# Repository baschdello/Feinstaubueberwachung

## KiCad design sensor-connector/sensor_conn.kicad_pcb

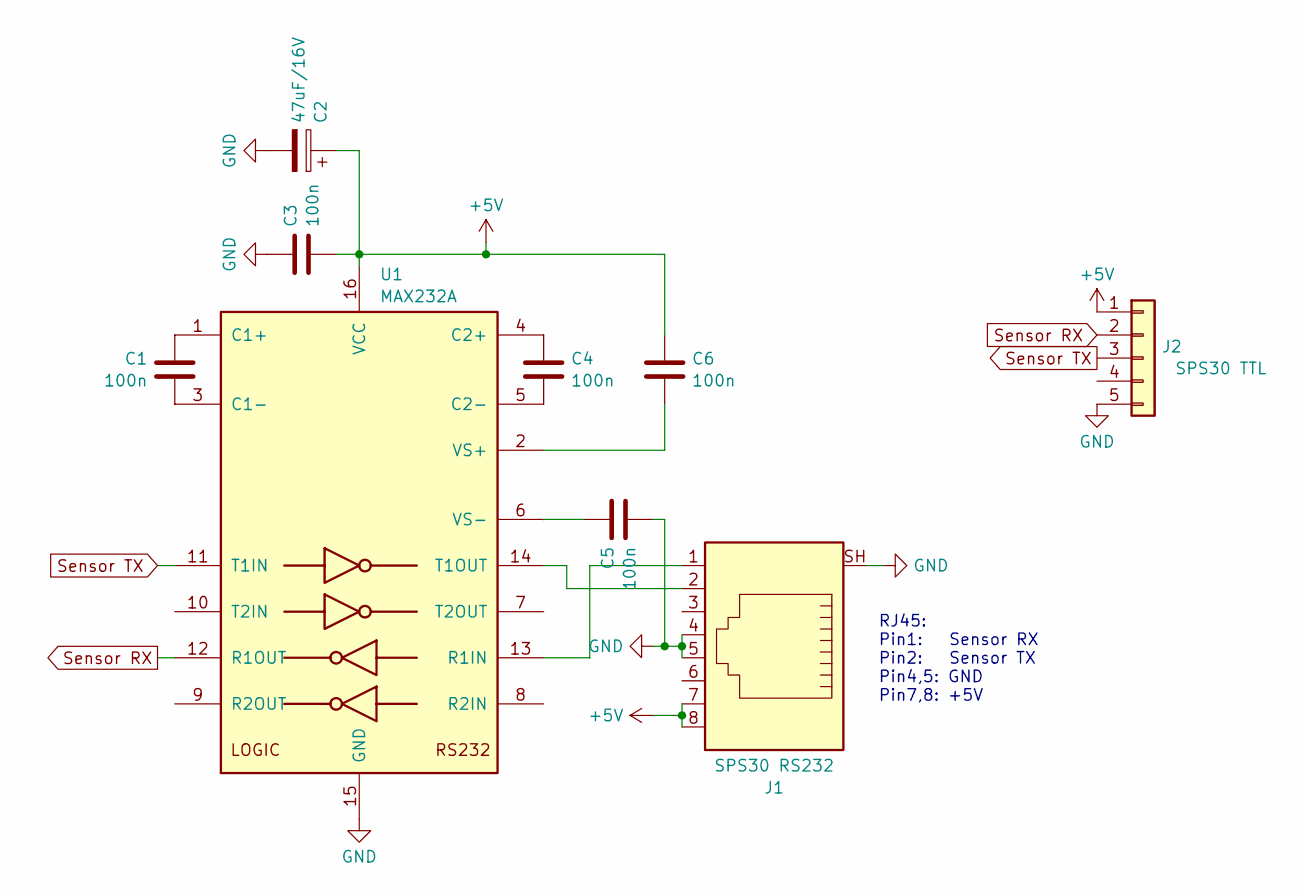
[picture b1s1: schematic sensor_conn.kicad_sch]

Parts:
C1, C3, C4, C5, C6: 100n; C_0603_1608Metric; LCSC C14663
C2: 47uF/16V; CP_Radial_D8.0mm_P3.50mm
J1: SPS30 RS232; RJ45_Ninigi_GE
J2: SPS30 TTL; JST_ZH_B5B-ZR_1x5_P1.50mm_Vertical
U1: MAX232A; SO-16_3.9x9.9mm_P1.27mm

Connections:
+5V: C2.1, C3.2, C6.1, J1.7, J1.8, J2.1, U1.16 (VCC)
GND: C2.2, C3.1, C5.2, J1.4, J1.5, J1.SH, J2.5, U1.15 (GND)
unnamed: C1.1, U1.1 (C1+)
unnamed: C1.2, U1.3 (C1-)
unnamed: C4.1, U1.4 (C2+)
unnamed: C4.2, U1.5 (C2-)
unnamed: J1.1, U1.13 (R1IN)
unnamed: J1.2, U1.14 (T1OUT)
unnamed: C6.2, U1.2 (VS+)
unnamed: C5.1, U1.6 (VS-)
Sensor RX: J2.2, U1.12 (R1OUT)
Sensor TX: J2.3, U1.11 (T1IN)

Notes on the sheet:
RJ45: Pin1: Sensor RX Pin2: Sensor TX Pin4,5: GND Pin7,8: +5V

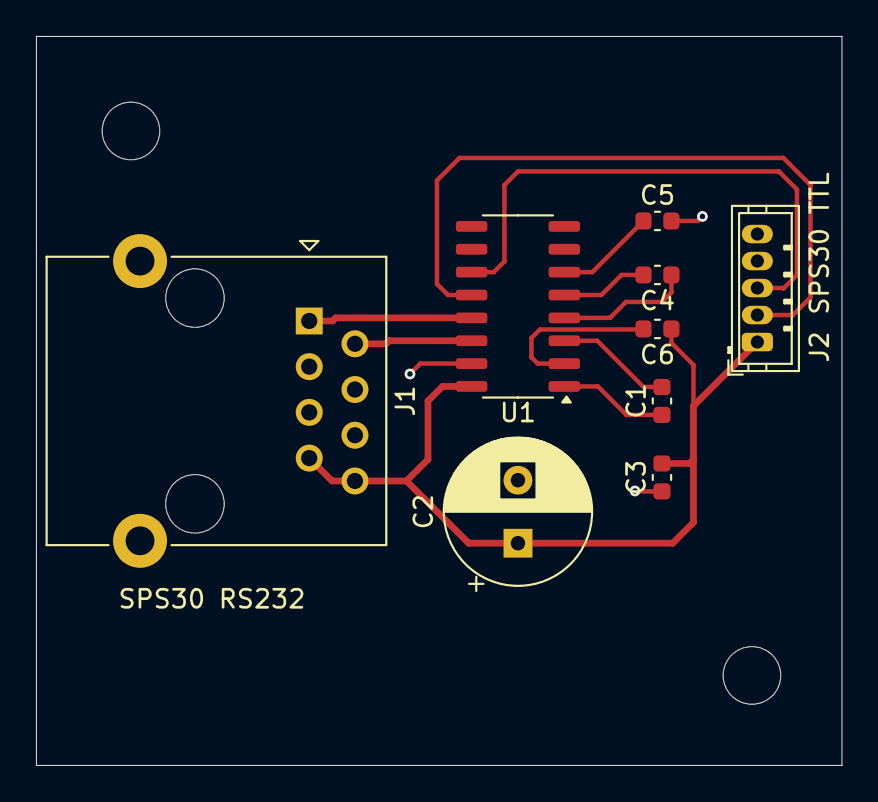
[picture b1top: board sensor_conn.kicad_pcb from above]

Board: 2 copper layers, 44.8 x 40.5 mm, 9 parts (0 on the bottom side), 12 nets.

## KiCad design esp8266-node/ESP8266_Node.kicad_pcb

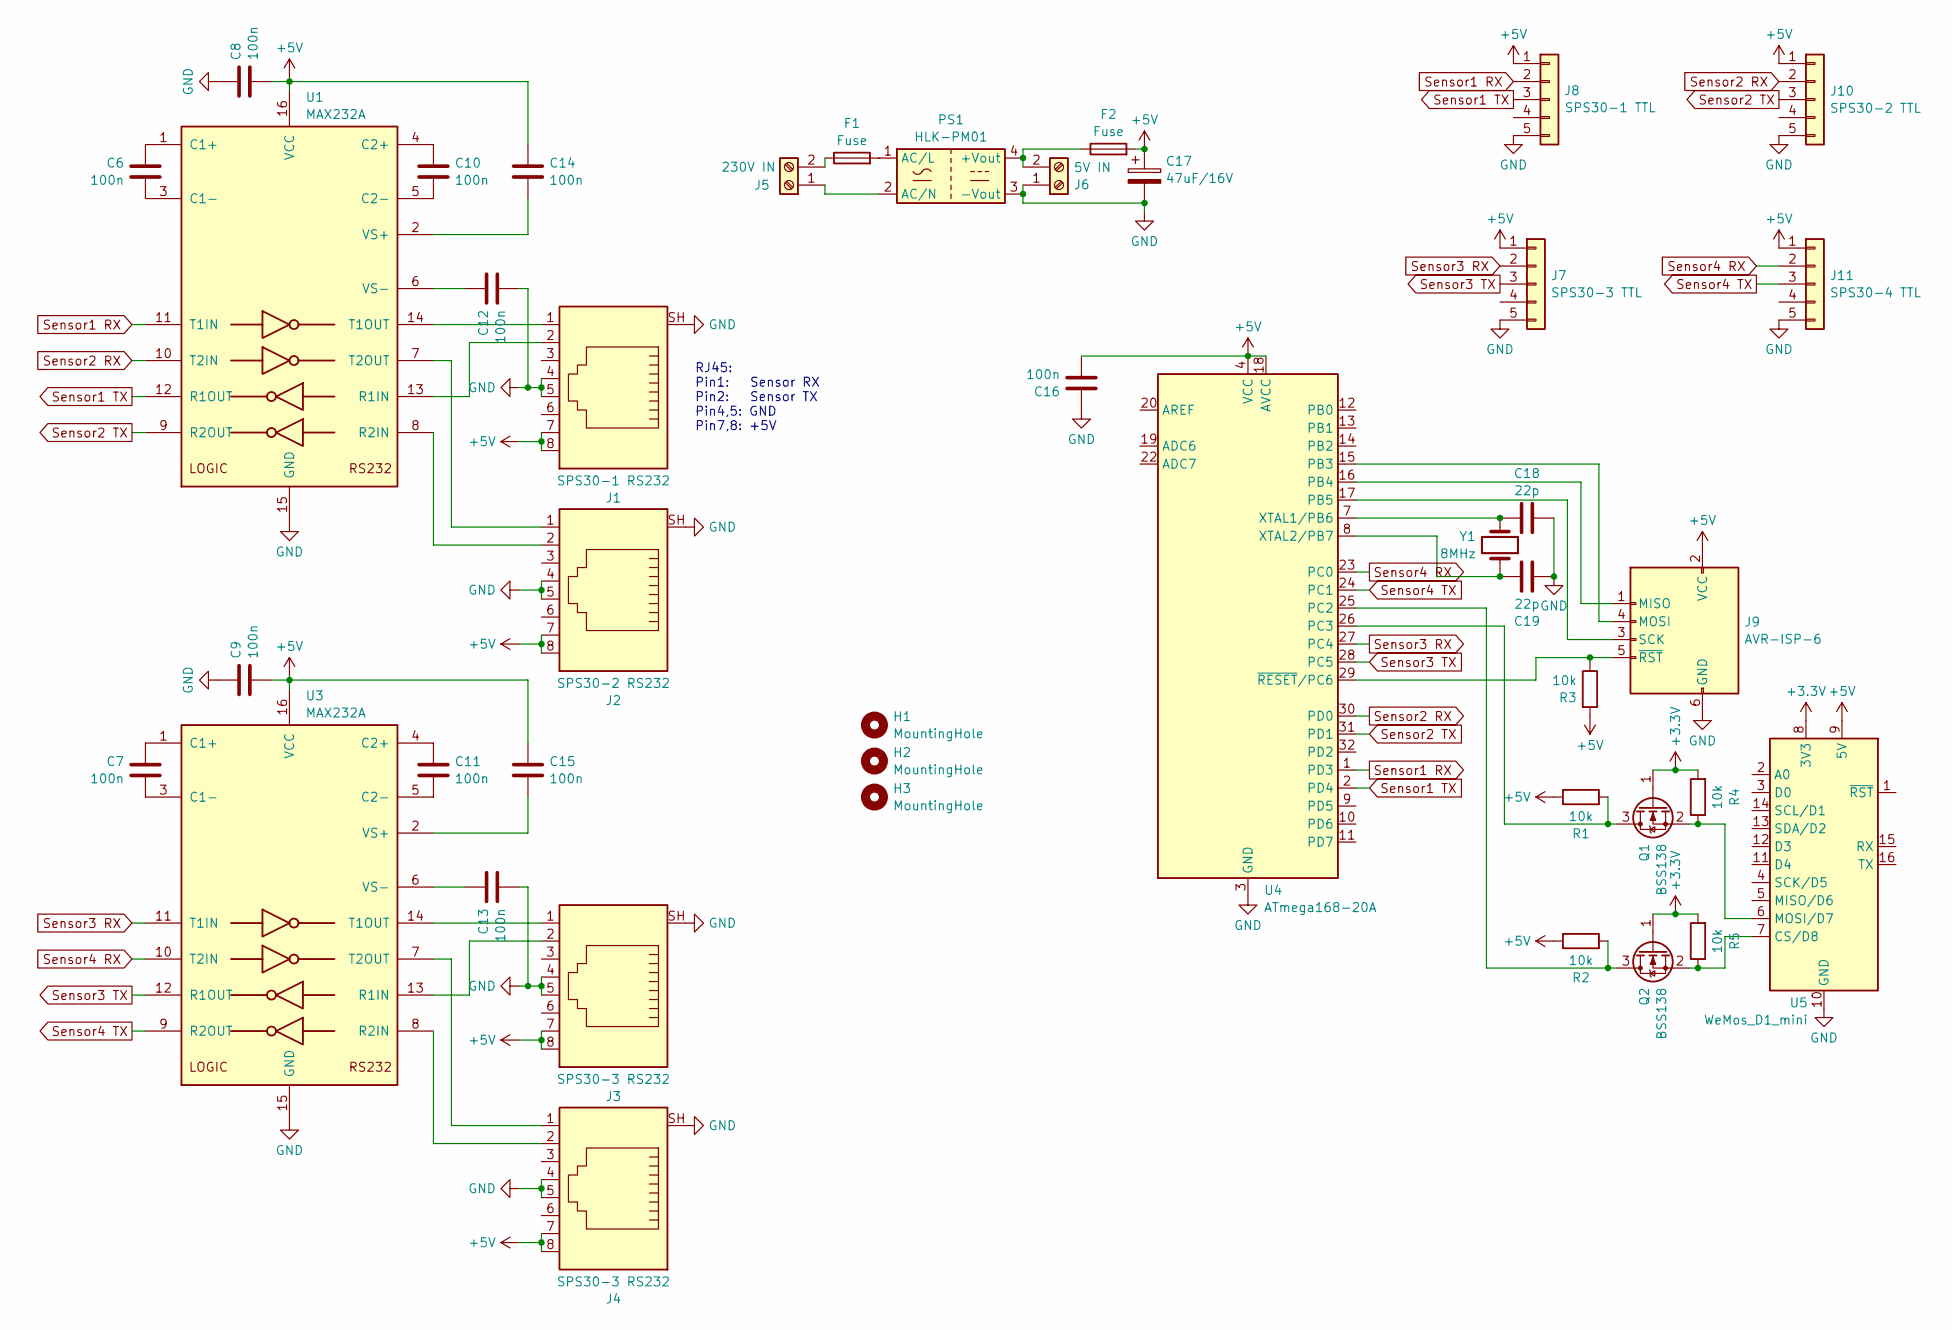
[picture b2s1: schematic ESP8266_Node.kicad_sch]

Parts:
C6, C7, C8, C9, C10, C11, C12, C13, C14, C15, C16: 100n; C_0603_1608Metric; LCSC C14663
C17: 47uF/16V; CP_Radial_D8.0mm_P3.50mm
C18, C19: 22p; C_0603_1608Metric; LCSC C1653
F1, F2: Fuse; Fuseholder_TR5_Littelfuse_No560_No460
H1, H2, H3: MountingHole; MountingHole_3.2mm_M3_ISO14580
J1: SPS30-1 RS232; RJ45_Ninigi_GE
J2: SPS30-2 RS232; RJ45_Ninigi_GE
J3, J4: SPS30-3 RS232; RJ45_Ninigi_GE
J5: 230V IN; TerminalBlock_MetzConnect_Type094_RT03502HBLU_1x02_P5.00mm_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
J6: 5V IN; TerminalBlock_MetzConnect_Type094_RT03502HBLU_1x02_P5.00mm_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
J7: SPS30-3 TTL; JST_ZH_B5B-ZR_1x5_P1.50mm_Vertical
J8: SPS30-1 TTL; JST_ZH_B5B-ZR_1x5_P1.50mm_Vertical
J9: AVR-ISP-6; IDC-Header_2x03_P2.54mm_Vertical
J10: SPS30-2 TTL; JST_ZH_B5B-ZR_1x5_P1.50mm_Vertical
J11: SPS30-4 TTL; JST_ZH_B5B-ZR_1x5_P1.50mm_Vertical
PS1: HLK-PM01; Converter_ACDC_Hi-Link_HLK-PMxx
Q1, Q2: BSS138; SOT-23; LCSC C8545
R1, R2, R3, R4, R5: 10k; R_0603_1608Metric; LCSC C25804
U1, U3: MAX232A; SO-16_3.9x9.9mm_P1.27mm
U4: ATmega168-20A; TQFP-32_7x7mm_P0.8mm
U5: WeMos_D1_mini; WEMOS_D1_mini_light
Y1: 8MHz; Crystal_SMD_5032-2Pin_5.0x3.2mm; LCSC C115962

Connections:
+3.3V: Q1.1 (G), Q2.1 (G), R4.2, R5.2, U5.8 (3V3)
+5V: C8.2, C9.2, C14.1, C15.1, C16.2, C17.1, F2.2, J1.7, J1.8, J2.7, J2.8, J3.7, J3.8, J4.7, J4.8, J7.1, J8.1, J9.2 (VCC), J10.1, J11.1, R1.1, R2.1, R3.2, U1.16 (VCC), U3.16 (VCC), U4.4 (VCC), U4.6 (VCC), U4.18 (AVCC), U5.9 (5V)
GND: C8.1, C9.1, C12.2, C13.2, C16.1, C17.2, C18.2, C19.1, J1.4, J1.5, J1.SH, J2.4, J2.5, J2.SH, J3.4, J3.5, J3.SH, J4.4, J4.5, J4.SH, J6.1, J7.5, J8.5, J9.6 (GND), J10.5, J11.5, PS1.3 (-Vout), U1.15 (GND), U3.15 (GND), U4.3 (GND), U4.5 (GND), U4.21 (GND), U5.10 (GND)
unnamed: J5.1, PS1.2 (AC/N)
unnamed: F1.1, J5.2
unnamed: F2.1, J6.2, PS1.4 (+Vout)
unnamed: J9.1 (MISO), U4.16 (PB4)
unnamed: J9.4 (MOSI), U4.15 (PB3)
unnamed: J9.3 (SCK), U4.17 (PB5)
unnamed: J9.5 (~RST), R3.1, U4.29 (~RESET/PC6)
unnamed: F1.2, PS1.1 (AC/L)
unnamed: Q1.3 (D), R1.2, U4.26 (PC3)
unnamed: Q1.2 (S), R4.1, U5.6 (MOSI/D7)
unnamed: Q2.3 (D), R2.2, U4.25 (PC2)
unnamed: Q2.2 (S), R5.1, U5.7 (CS/D8)
unnamed: C6.1, U1.1 (C1+)
unnamed: C6.2, U1.3 (C1-)
unnamed: C10.1, U1.4 (C2+)
unnamed: C10.2, U1.5 (C2-)
unnamed: J1.2, U1.13 (R1IN)
unnamed: J2.2, U1.8 (R2IN)
unnamed: J1.1, U1.14 (T1OUT)
unnamed: J2.1, U1.7 (T2OUT)
unnamed: C14.2, U1.2 (VS+)
unnamed: C12.1, U1.6 (VS-)
unnamed: C7.1, U3.1 (C1+)
unnamed: C7.2, U3.3 (C1-)
unnamed: C11.1, U3.4 (C2+)
unnamed: C11.2, U3.5 (C2-)
unnamed: J3.2, U3.13 (R1IN)
unnamed: J4.2, U3.8 (R2IN)
unnamed: J3.1, U3.14 (T1OUT)
unnamed: J4.1, U3.7 (T2OUT)
unnamed: C15.2, U3.2 (VS+)
unnamed: C13.1, U3.6 (VS-)
unnamed: C18.1, U4.7 (XTAL1/PB6), Y1.2
unnamed: C19.2, U4.8 (XTAL2/PB7), Y1.1
Sensor1 RX: J8.2, U1.11 (T1IN), U4.1 (PD3)
Sensor1 TX: J8.3, U1.12 (R1OUT), U4.2 (PD4)
Sensor2 RX: J10.2, U1.10 (T2IN), U4.30 (PD0)
Sensor2 TX: J10.3, U1.9 (R2OUT), U4.31 (PD1)
Sensor3 RX: J7.2, U3.11 (T1IN), U4.27 (PC4)
Sensor3 TX: J7.3, U3.12 (R1OUT), U4.28 (PC5)
Sensor4 RX: J11.2, U3.10 (T2IN), U4.23 (PC0)
Sensor4 TX: J11.3, U3.9 (R2OUT), U4.24 (PC1)

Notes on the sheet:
RJ45: Pin1: Sensor RX Pin2: Sensor TX Pin4,5: GND Pin7,8: +5V

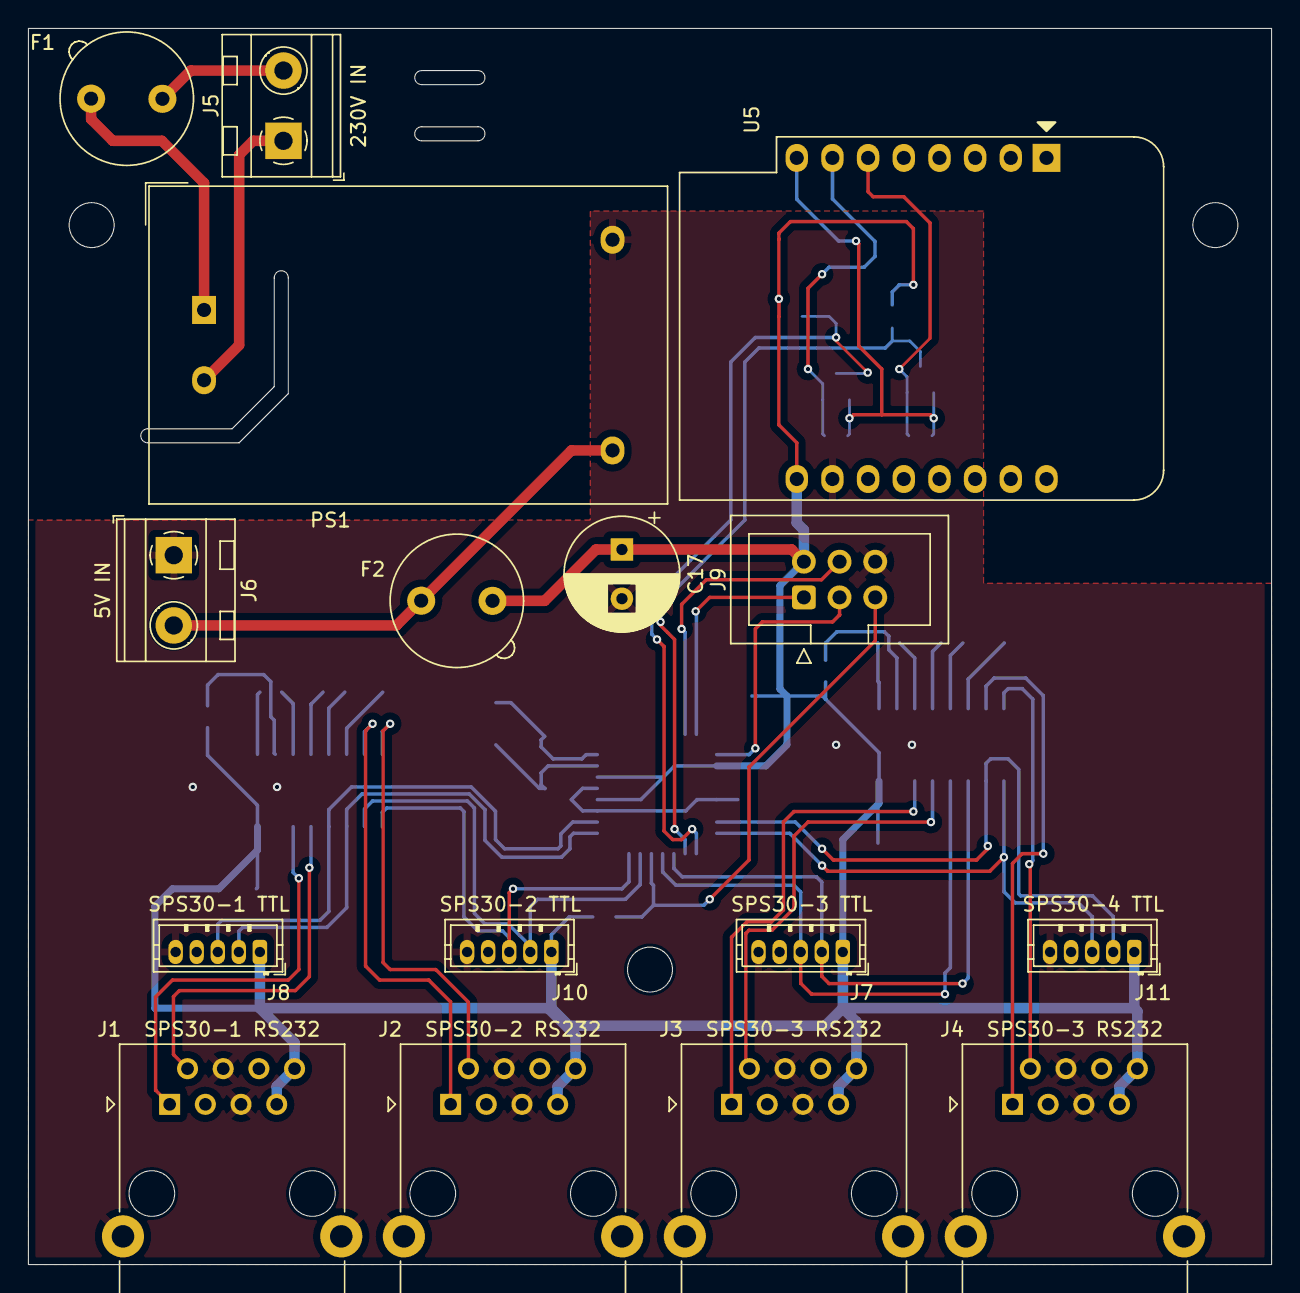
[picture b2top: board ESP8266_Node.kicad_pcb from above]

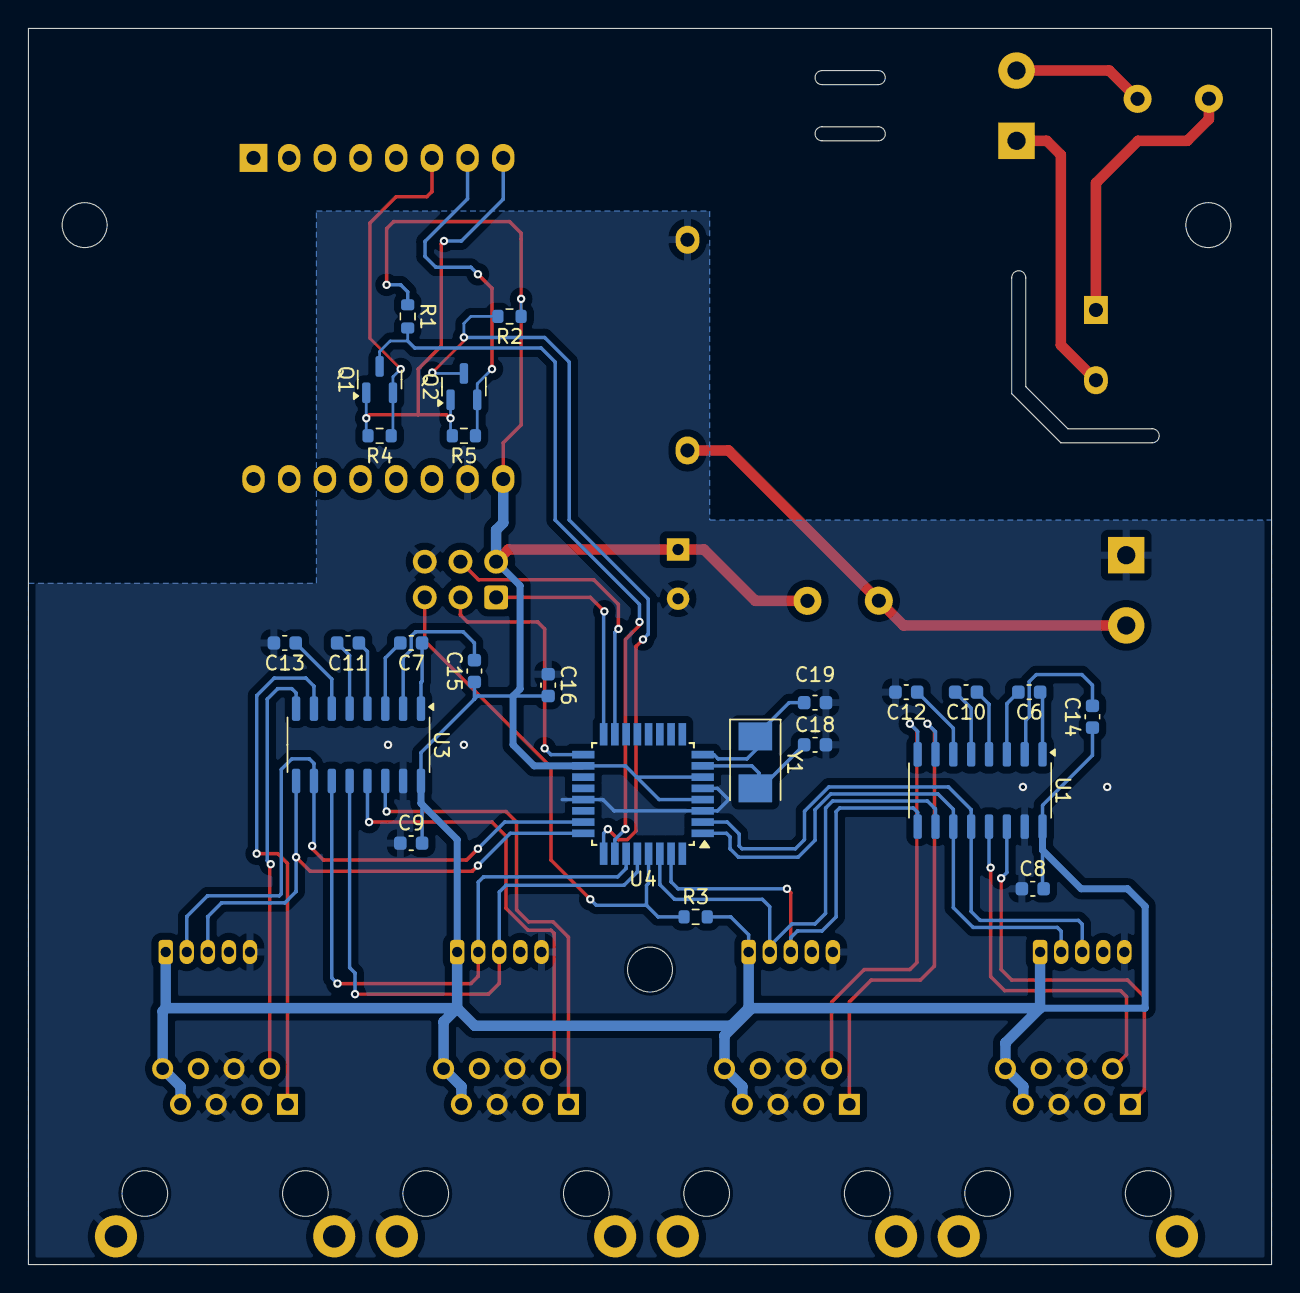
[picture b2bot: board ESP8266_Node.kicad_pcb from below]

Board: 2 copper layers, 88.5 x 88.0 mm, 43 parts (24 on the bottom side), 45 nets.

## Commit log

2024-07-04 changed mounting holes
